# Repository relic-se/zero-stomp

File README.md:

# Zero Stomp
Programmable multi-effects guitar pedal based on the RP2040/RP2350-Zero and WM8960 audio codec. Supports CircuitPython 9.2+.

**More info coming soon!**

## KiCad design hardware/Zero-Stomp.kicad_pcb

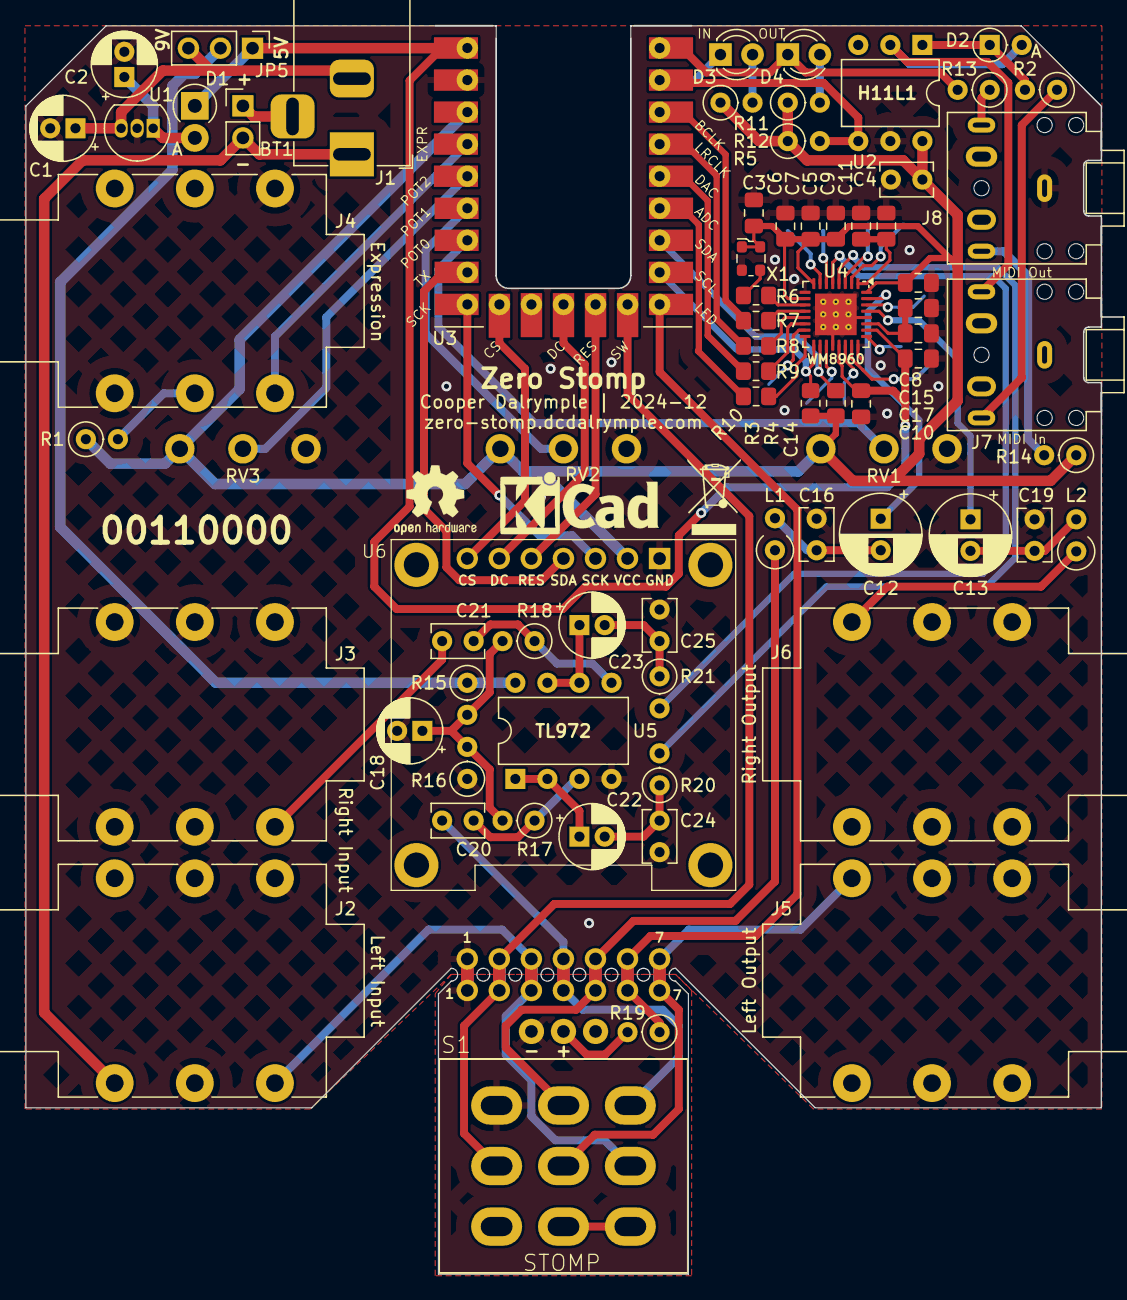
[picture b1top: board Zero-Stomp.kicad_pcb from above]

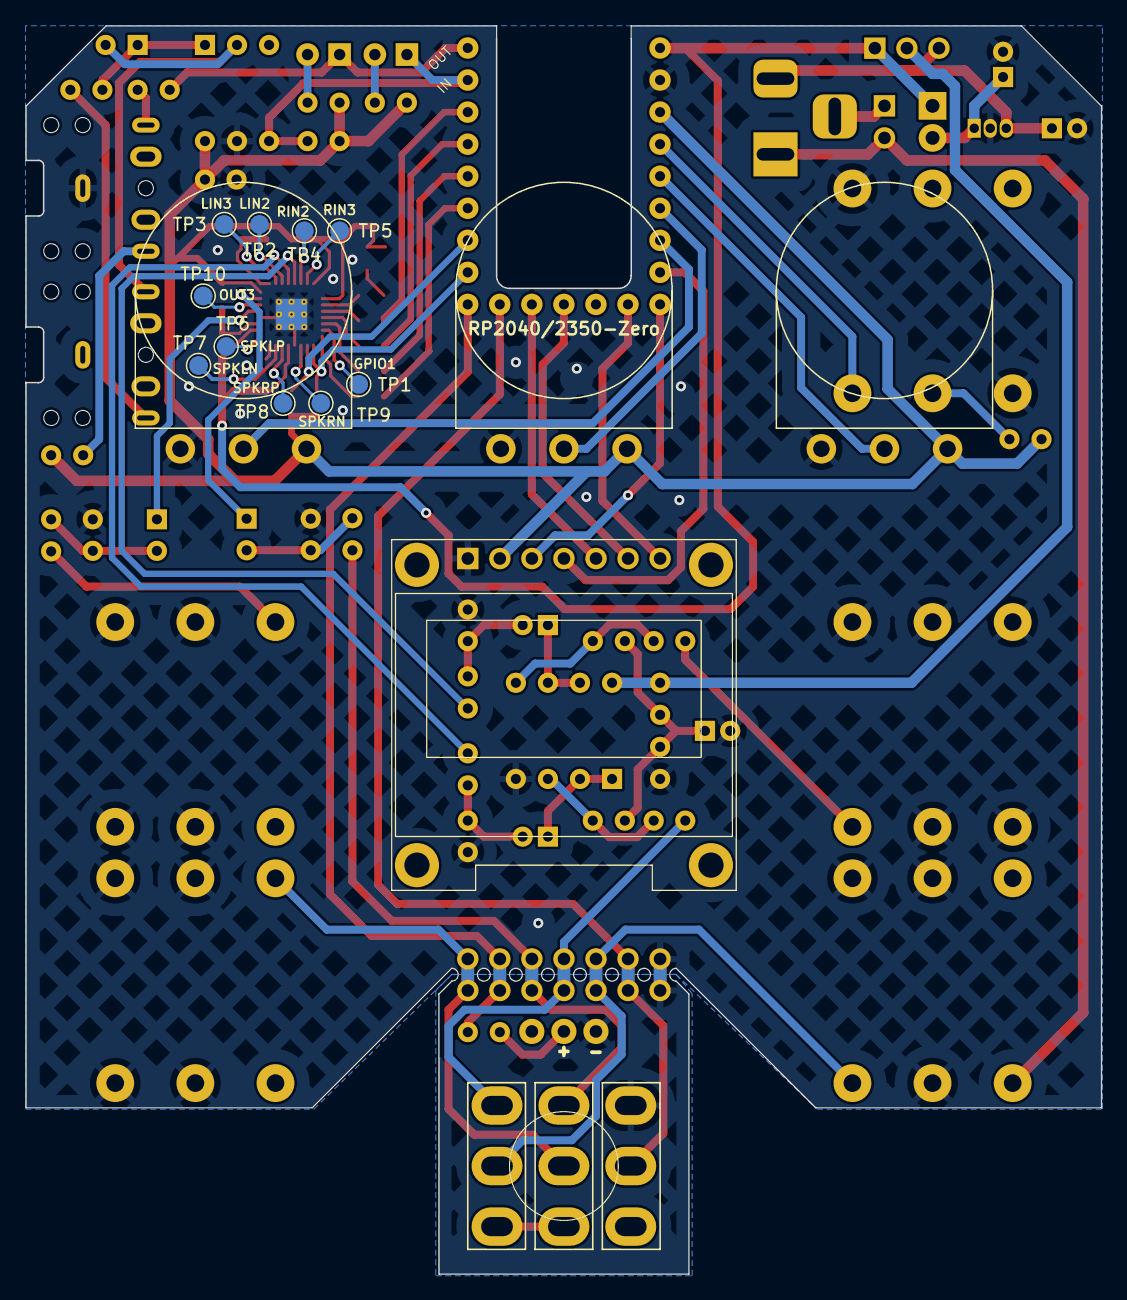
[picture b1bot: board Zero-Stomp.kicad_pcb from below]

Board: 2 copper layers, 85.2 x 98.9 mm, 91 parts (15 on the bottom side), 81 nets.

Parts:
3D?: HAMMOND-1590BB
BT1: Battery; PinHeader_1x02_P2.54mm_Vertical
C1, C2, C22, C23: 1u; CP_Radial_D5.0mm_P2.00mm
C3: 10n; C_0805_2012Metric_Pad1.18x1.45mm_HandSolder
C4: 1u; C_Rect_L4.0mm_W2.5mm_P2.50mm
C5, C6, C7, C8, C11, C17: 0u1; C_0805_2012Metric_Pad1.18x1.45mm_HandSolder
C9, C15: 10u; C_0805_2012Metric_Pad1.18x1.45mm_HandSolder
C10, C14: 4u7; C_0805_2012Metric_Pad1.18x1.45mm_HandSolder
C12, C13: 100u; CP_Radial_D6.3mm_P2.50mm
C16, C19, C20, C21: 0u1; C_Rect_L4.0mm_W2.5mm_P2.50mm
C18: 47u; CP_Radial_D5.0mm_P2.00mm
C24, C25: 33n; C_Rect_L4.0mm_W2.5mm_P2.50mm
D1: 1N5817; D_DO-41_SOD81_P2.54mm_Vertical_AnodeUp
D2: 1N4148; D_DO-35_SOD27_P2.54mm_Vertical_AnodeUp
D3: IN; LED_D3.0mm
D4: OUT; LED_D3.0mm
J1: Power; BarrelJack_Horizontal
J2: Left Input; Jack_6.35mm_Neutrik_NMJ6HFD2_Horizontal
J3: Right Input; Jack_6.35mm_Neutrik_NMJ6HFD2_Horizontal
J4: Expression; Jack_6.35mm_Neutrik_NMJ6HFD2_Horizontal
J5: Left Output; Jack_6.35mm_Neutrik_NMJ6HFD2_Horizontal
J6: Right Output; Jack_6.35mm_Neutrik_NMJ6HFD2_Horizontal
J7: MIDI_IN; Jack_3.5mm_CUI_SJ1-3525N_Horizontal
J8: MIDI_OUT; Jack_3.5mm_CUI_SJ1-3525N_Horizontal
JP1: 3; Jumper_2_THT_P2.54mm
JP2: 4; Jumper_2_THT_P2.54mm
JP3: 5; Jumper_2_THT_P2.54mm
JP4: 7; Jumper_2_THT_P2.54mm
JP5: PWR_SEL; PinHeader_1x03_P2.54mm_Vertical
JP6: 6; Jumper_2_THT_P2.54mm
JP7: 2; Jumper_2_THT_P2.54mm
JP8: 1; Jumper_2_THT_P2.54mm
L1, L2: 47uH; L_Axial_L6.6mm_D2.7mm_P2.54mm_Vertical_Vishay_IM-2
R1, R11, R12, R19: 2k2; R_Axial_DIN0207_L6.3mm_D2.5mm_P2.54mm_Vertical
R2, R14: 220; R_Axial_DIN0207_L6.3mm_D2.5mm_P2.54mm_Vertical
R3, R4: 2k2; R_0805_2012Metric_Pad1.20x1.40mm_HandSolder
R5: 470; R_Axial_DIN0207_L6.3mm_D2.5mm_P2.54mm_Vertical
R6, R7, R8, R9, R10: 10; R_0805_2012Metric_Pad1.20x1.40mm_HandSolder
R13: 10; R_Axial_DIN0207_L6.3mm_D2.5mm_P2.54mm_Vertical
R15, R16: 2M2; R_Axial_DIN0207_L6.3mm_D2.5mm_P2.54mm_Vertical
R17, R18: 1M; R_Axial_DIN0207_L6.3mm_D2.5mm_P2.54mm_Vertical
R20, R21: 100; R_Axial_DIN0207_L6.3mm_D2.5mm_P2.54mm_Vertical
RV1, RV2, RV3: 100k; Potentiometer_Omeg_PC16BU_Vertical
S1: STOMP; STOMP-3PDT-LED
TP1, TP2, TP3, TP4, TP5, TP6, TP7, TP8, TP9, TP10: TestPoint; TestPoint_Pad_D1.5mm
U1: L78L05_TO92; TO-92_Inline
U2: H11L1; DIP-6_W7.62mm
U3: RP2040-Zero; RP2040 Zero
U4: WM8960CGEFL/V; QFN-32-1EP_5x5mm_P0.5mm_EP3.3x3.3mm_ThermalVias
U5: TL972; DIP-8_W7.62mm
U6: SSD1306-OLED-SPI; SSD1306-OLED-SPI-0.96
X1: 24MHz; Oscillator_SMD_ECS_2520MV-xxx-xx-4Pin_2.5x2.0mm

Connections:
+3V3: C3.1, C4.1, C5.1, C6.1, C7.1, C8.1, R1.1, R3.1, R4.1, R5.1, R11.1, R12.1, R14.1, RV1.1, RV2.1, RV3.1, U2.6, U3.3 (3V3), U4.8 (DCVDD), U4.10 (DBVDD), U4.32 (AVDD), U6.2 (VCC), X1.1 (Tri-State), X1.4 (VDD)
+5V: C10.1, C14.1, D1.1 (K), JP5.1 (A), U3.1 (5V), U4.21 (SPKVDD2), U4.26 (SPKVDD1)
+9V: C1.1, J1.2, JP5.3 (B), U1.3 (VI)
/AMP_PWR: JP5.2 (C), R15.1, U5.8 (V+)
EXPR: J4.T, U3.4 (GP29)
GND: C1.2, C2.2, C3.2, C4.2, C5.2, C6.2, C7.2, C8.2, C9.2, C10.2, C11.2, C14.2, C15.2, C16.2, C17.2, C18.2, C19.2, C24.2, C25.2, J2.R, J2.RN, J2.TN, J3.R, J3.RN, J3.S, J3.SN, J3.TN, J4.S, J4.TN, J5.R, J5.RN, J5.S, J5.SN, J6.R, J6.RN, J6.S, J6.SN, J8.S, JP8.1 (A), R16.1, RV1.3, RV2.3, RV3.3, U1.2 (GND), U2.5, U3.2 (GND), U4.9 (DGND), U4.20 (SPKGND2), U4.24 (SPKGND1), U4.28 (AGND), U4.33 (GND), U5.4 (V-), U6.1 (GND), X1.2 (GND)
GND2: JP8.2 (B), S1.P$7 (O), S1.P$11 (K)
I2C_SCL: R3.2, U3.17 (GP7), U4.17 (SCLK)
I2C_SDA: R4.2, U3.16 (GP6), U4.18 (SDIN)
I2S_ADC: R10.1, U3.15 (GP5)
I2S_BCLK: R7.1, U3.12 (GP2)
I2S_DAC: R9.1, U3.14 (GP4)
I2S_LRCLK: R8.1, U3.13 (GP3)
INST_L: C20.1, JP2.2 (B)
INST_R: C21.1, J3.T
LED: JP6.2 (B), U3.18 (GP8)
LINE_L: R20.2, U4.4 (LINPUT1)
LINE_R: R21.2, U4.5 (RINPUT1)
unnamed: BT1.1 (+), J1.3
unnamed: BT1.2 (-), J1.1, J2.S
unnamed: C12.2, C16.1, L1.2
unnamed: C13.2, C19.1, L2.2
unnamed: C18.1, R15.2, R16.2, R17.2, R18.2
unnamed: C22.2, C24.1, R20.1
unnamed: C23.2, C25.1, R21.1
unnamed: C2.1, D1.2 (A), U1.1 (VO)
unnamed: D2.2 (A), J7.T, U2.2
unnamed: D2.1 (K), R2.2, U2.1
unnamed: D3.2 (A), R11.2
unnamed: D4.2 (A), R12.2
unnamed: J4.R, R1.2
unnamed: J7.R, R2.1
unnamed: J8.R, R14.2
unnamed: J8.T, R13.1
unnamed: J2.T, JP1.1 (A)
unnamed: JP1.2 (B), S1.P$2
unnamed: JP2.1 (A), S1.P$1 (O)
unnamed: JP3.2 (B), S1.P$4 (O)
unnamed: JP4.1 (A), S1.P$5
unnamed: J5.T, JP4.2 (B)
unnamed: JP6.1 (A), R19.1
unnamed: JP7.1 (A), S1.P$8
unnamed: S1.P$3 (S), S1.P$6 (S)
unnamed: R19.2, S1.P$10 (A)
unnamed: R10.2, U4.16 (ADCDAT)
unnamed: TP1.1, U4.15 (ADCLRC/GPIO1)
unnamed: R7.2, U4.12 (BCLK)
unnamed: R9.2, U4.14 (DACDAT)
unnamed: R8.2, U4.13 (DACLRC)
unnamed: C12.1, U4.31 (HP_L)
unnamed: C13.1, U4.29 (HP_R)
unnamed: TP2.1, U4.3 (LINPUT2)
unnamed: TP3.1, U4.2 (LINPUT3/JD2)
unnamed: R6.2, U4.11 (MCLK)
unnamed: C9.1, C11.1, U4.1 (MICBIAS)
unnamed: TP10.1, U4.30 (OUT3)
unnamed: TP4.1, U4.6 (RINPUT2)
unnamed: TP5.1, U4.7 (RINPUT3/JD3)
unnamed: TP7.1, U4.23 (SPK_LN)
unnamed: TP6.1, U4.25 (SPK_LP)
unnamed: TP9.1, U4.19 (SPK_RN)
unnamed: TP8.1, U4.22 (SPK_RP)
unnamed: C15.1, C17.1, U4.27 (VMID)
unnamed: C20.2, R17.1, U5.3 (+)
unnamed: C22.1, U5.1, U5.2 (-)
unnamed: C21.2, R18.1, U5.5 (+)
unnamed: C23.1, U5.6 (-), U5.7
unnamed: R6.1, X1.3 (OUT)
OLED_DC: U3.21 (GP11), U6.6 (DC)
OLED_RES: U3.22 (GP10), U6.5 (RES)
OUT_L: JP3.1 (A), L1.1
OUT_R: J6.T, L2.1
POT0: RV1.2, U3.7 (GP26)
POT1: RV2.2, U3.6 (GP27)
POT2: RV3.2, U3.5 (GP28)
SPI_CS: U3.19 (GP13), U6.7 (CS)
SPI_SCK: U3.9 (GP14), U6.3 (SCK)
SPI_TX: U3.8 (GP15), U6.4 (SDA)
SW: JP7.2 (B), U3.23 (GP9)
UART_RX: D3.1 (K), R5.2, U2.4, U3.11 (GP1)
UART_TX: D4.1 (K), R13.2, U3.10 (GP0)

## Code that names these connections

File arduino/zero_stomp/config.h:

// SPDX-FileCopyrightText: Copyright (c) 2025 Cooper Dalrymple
//
// SPDX-License-Identifier: GPLv3

#ifndef _CONFIG_H
#define _CONFIG_H

// Pin Configuration

#define UART_TX 0
#define UART_RX 1

#define I2S_BCLK 2
#define I2S_LRCLK 3
#define I2S_DOUT 4
#define I2S_DIN 5

#define I2C_SDA 6
#define I2C_SCL 7
#define I2C_WIRE Wire1

#define STOMP_LED 8
#define STOMP_SWITCH 9

#define DISPLAY_RESET 10
#define DISPLAY_DC 11
#define DISPLAY_CS 13
#define DISPLAY_SCK 14
#define DISPLAY_TX 15

#define ADC_0 26
#define ADC_1 27
#define ADC_2 28
#define ADC_EXPR 29
#define NUM_POTS 3

// Constants

#define DISPLAY_WIDTH 128
#define DISPLAY_HEIGHT 64

#define SAMPLE_RATE 48000
#define BITS_PER_SAMPLE 16
#define CHANNELS 2

#define SWITCH_SHORT_DURATION 400 // ms

#endif

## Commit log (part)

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2024-10-11 Added RP2040-Zero-KiCAD submodule.
2024-10-11 Updated .gitignore.
2024-10-11 Added custom libraries and 3d models.
2024-10-11 Added TAC5212 symbol (timchinowsky/tac5).
2024-12-17 Initial hardware design completed.
2024-12-17 Move hardware design into subfolder.
2024-12-17 Initial software configuration.
2024-12-18 Initial hardware abstraction library.
2024-12-18 Tuner effect.
2024-12-18 Move CircuitPython firmware into subfolder.
2024-12-19 Removed simplemath requirement.
2024-12-19 Rename I2S data pins.
2024-12-19 Improved knob, switch, and led control systems.
2024-12-19 Unsupported delay example.
2024-12-19 Unsupported distortion example.
2024-12-19 Add expression support to distortion effect.
2024-12-19 Knob assignment to object attribute.
2024-12-19 Added Wah effect.
2024-12-19 Added Tremolo effect.
2024-12-22 Add methods to access settings and manage supervisor.
2024-12-22 Use triple click to load next program.
2025-01-20 Added 3d print models.
2025-01-20 Various bug fixes and I2S implementation.
2025-01-20 Minor adjustments to hardware design.
2025-01-20 Improve knob control.
2025-01-20 Add samples signed constant.
2025-01-20 Additional improvements to tremolo and delay effects.
2025-01-20 Use codec output volume for tremolo instead of controlling digitally.
2025-01-20 Increase led pwm frequency to prevent audible noise in output.
2025-01-20 Configure storage at boot.
2025-01-21 Fix app switching.
2025-01-21 Remove old I2SIn/I2SOut objects.
2025-01-22 Improve mix curve.
2025-01-23 Change delay lfo scale range.
2025-01-23 Change device usb label.
2025-01-23 Updated Tuner to use `pio_i2s`.
2025-01-23 Graphic EQ effect.
2025-01-23 Added test script.
2025-01-23 Reduce time of short click duration.
2025-01-23 Initial arduino test using AudioTools library.
2025-01-24 Updated arduino firmware to use dedicated library.
2025-01-24 Remove arduino example.
2025-01-24 Add arduino library as submodule.
2025-02-03 Added basic on-board RP2350A to schematic
2025-03-14 Schematic revision completed
    New codec, TLV320AIC3104. Improved power isolation. More control inputs. Modular design.
2025-03-14 Reset references and remove THT footprint assignments.
2025-03-14 Rename 100n to 0u1
2025-03-14 Footprint assignments
2025-03-18 Change connectors to JST SH
2025-03-18 Add power switch and bypass jumper
2025-03-18 Add test point to GPIO0
2025-03-18 Change out H11L1 with TLP2362
    For smaller footprint!
